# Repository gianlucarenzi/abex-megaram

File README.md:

Atari MegaRAM Cart for ABEX
=========================

This is a Atari MegaRAM Cart board, designed for the Atari PBI & ECI Bus EXtender
or ABEX for short.

This Atari MegaRAM is a PortB/PIA emulator which can expand the internal
memory of the Atari, using the memory mapped scheme used in the 80s/90s
like CompyShop, RAMbo and others.

Rendered Images
===============
# Front
# Back
# Overall

Hardware License
================
Copyright (C) 2018/2019 Gianluca Renzi <gianlucarenzi@eurek.it> <icjtqr@gmail.com>

The hardware of this project is released as free/open hardware under the
Creative Commons Attribution Share-Alike license. See `LICENSE.hw` for details.

Firmware License
================
Copyright (C) 2019 Gianluca Renzi <icjtqr@gmail.com>

The microcontroller firmware of this project is released as free software,
under the terms of the GNU General Public License v3, or later.  See
`LICENSE.sw` for details.

Software License
================
The host software (amigafloppy tool) is released as free software, under the
terms of the GNU General Public License v3, or later. See `LICENSE.sw` or licence.txt for
details.

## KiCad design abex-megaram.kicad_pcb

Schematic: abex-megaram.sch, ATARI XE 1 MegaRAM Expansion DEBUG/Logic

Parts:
C1: 100n; C_1206_HandSoldering
FT232RPi.1: CONN_01X03; Pin_Header_Straight_1x03
JP1: CONN_01X02; Pin_Header_Straight_1x02
JP2: CONN_01X04; Pin_Header_Angled_1x04
P1: 0877159106; BUS_PCIexpress_64pin
P2, P3, P4, P5: CONN_01X01; MountingHole
R1: 100K; R_1206_HandSoldering
R2: 0; R_1206_HandSoldering
SW1: SW_Push; SW_SPST_FSMSM_3D

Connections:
GND: C1.1, FT232RPi.1.1, JP1.2, JP2.1, P1.A1, P1.A5, P1.A9, P1.A13, P1.A17, P1.A21, P1.A25, P1.A29, P1.A32, P1.B17, P1.B21, P1.B25, R2.2, SW1.1; also elsewhere on the board
SWDCLK: JP2.3, P1.B29; also elsewhere on the board
SWDIO: JP2.2, P1.B27; also elsewhere on the board
SWDRST: C1.2, JP1.1, P1.B31, R1.1, SW1.2; also elsewhere on the board
UART_RX: FT232RPi.1.2; also elsewhere on the board
UART_TX: FT232RPi.1.3; also elsewhere on the board
VCC_3V3: JP2.4, P1.A3, P1.A7, P1.A11, P1.A15, P1.A19, P1.A23, P1.A27, P1.B19, P1.B23, R1.2; also elsewhere on the board
mA0: P1.B32; also elsewhere on the board
mA1: P1.B30; also elsewhere on the board
mA2: P1.B28; also elsewhere on the board
mA3: P1.B26; also elsewhere on the board
mA4: P1.B24; also elsewhere on the board
mA5: P1.B22; also elsewhere on the board
mA6: P1.B20; also elsewhere on the board
mA7: P1.B18; also elsewhere on the board
mA8: P1.B16; also elsewhere on the board
mA9: P1.B14; also elsewhere on the board
mA10: P1.B12; also elsewhere on the board
mA11: P1.B10; also elsewhere on the board
mA12: P1.B8; also elsewhere on the board
mA13: P1.B6; also elsewhere on the board
mA14: P1.B4; also elsewhere on the board
mA15: P1.B2; also elsewhere on the board
mAUDIO: P1.A6, R2.1
mD0: P1.B15; also elsewhere on the board
mD1: P1.B13; also elsewhere on the board
mD2: P1.B11; also elsewhere on the board
mD3: P1.B9; also elsewhere on the board
mD4: P1.B7; also elsewhere on the board
mD5: P1.B5; also elsewhere on the board
mD6: P1.B3; also elsewhere on the board
mD7: P1.B1; also elsewhere on the board
mPHI2: P1.A4; also elsewhere on the board
mR/~W: P1.A10; also elsewhere on the board
mRD4: P1.A24; also elsewhere on the board
mRD5: P1.A28; also elsewhere on the board
~mCCTL: P1.A30; also elsewhere on the board
~mD1XX: P1.A18; also elsewhere on the board
~mEXSEL: P1.A12; also elsewhere on the board
~mHALT: P1.A16; also elsewhere on the board
~mIRQ: P1.A14; also elsewhere on the board
~mMPD: P1.A20; also elsewhere on the board
~mREF: P1.A8; also elsewhere on the board
~mRST: P1.A2; also elsewhere on the board
~mS4: P1.A22; also elsewhere on the board
~mS5: P1.A26; also elsewhere on the board

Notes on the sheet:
DEBUG/PROGRAMMING SECTION MEMORY
MOUNTING HOLES
RESET BUTTON MEM
EXTENDED BUS PINS ARE CONNECTED IN THE SLOT BUT LEFT UNTRACKED
DNP
ABEX PCI EXPRESS CARD CONNECTOR 64 PIN
A31 is +5VDC. We do not need here

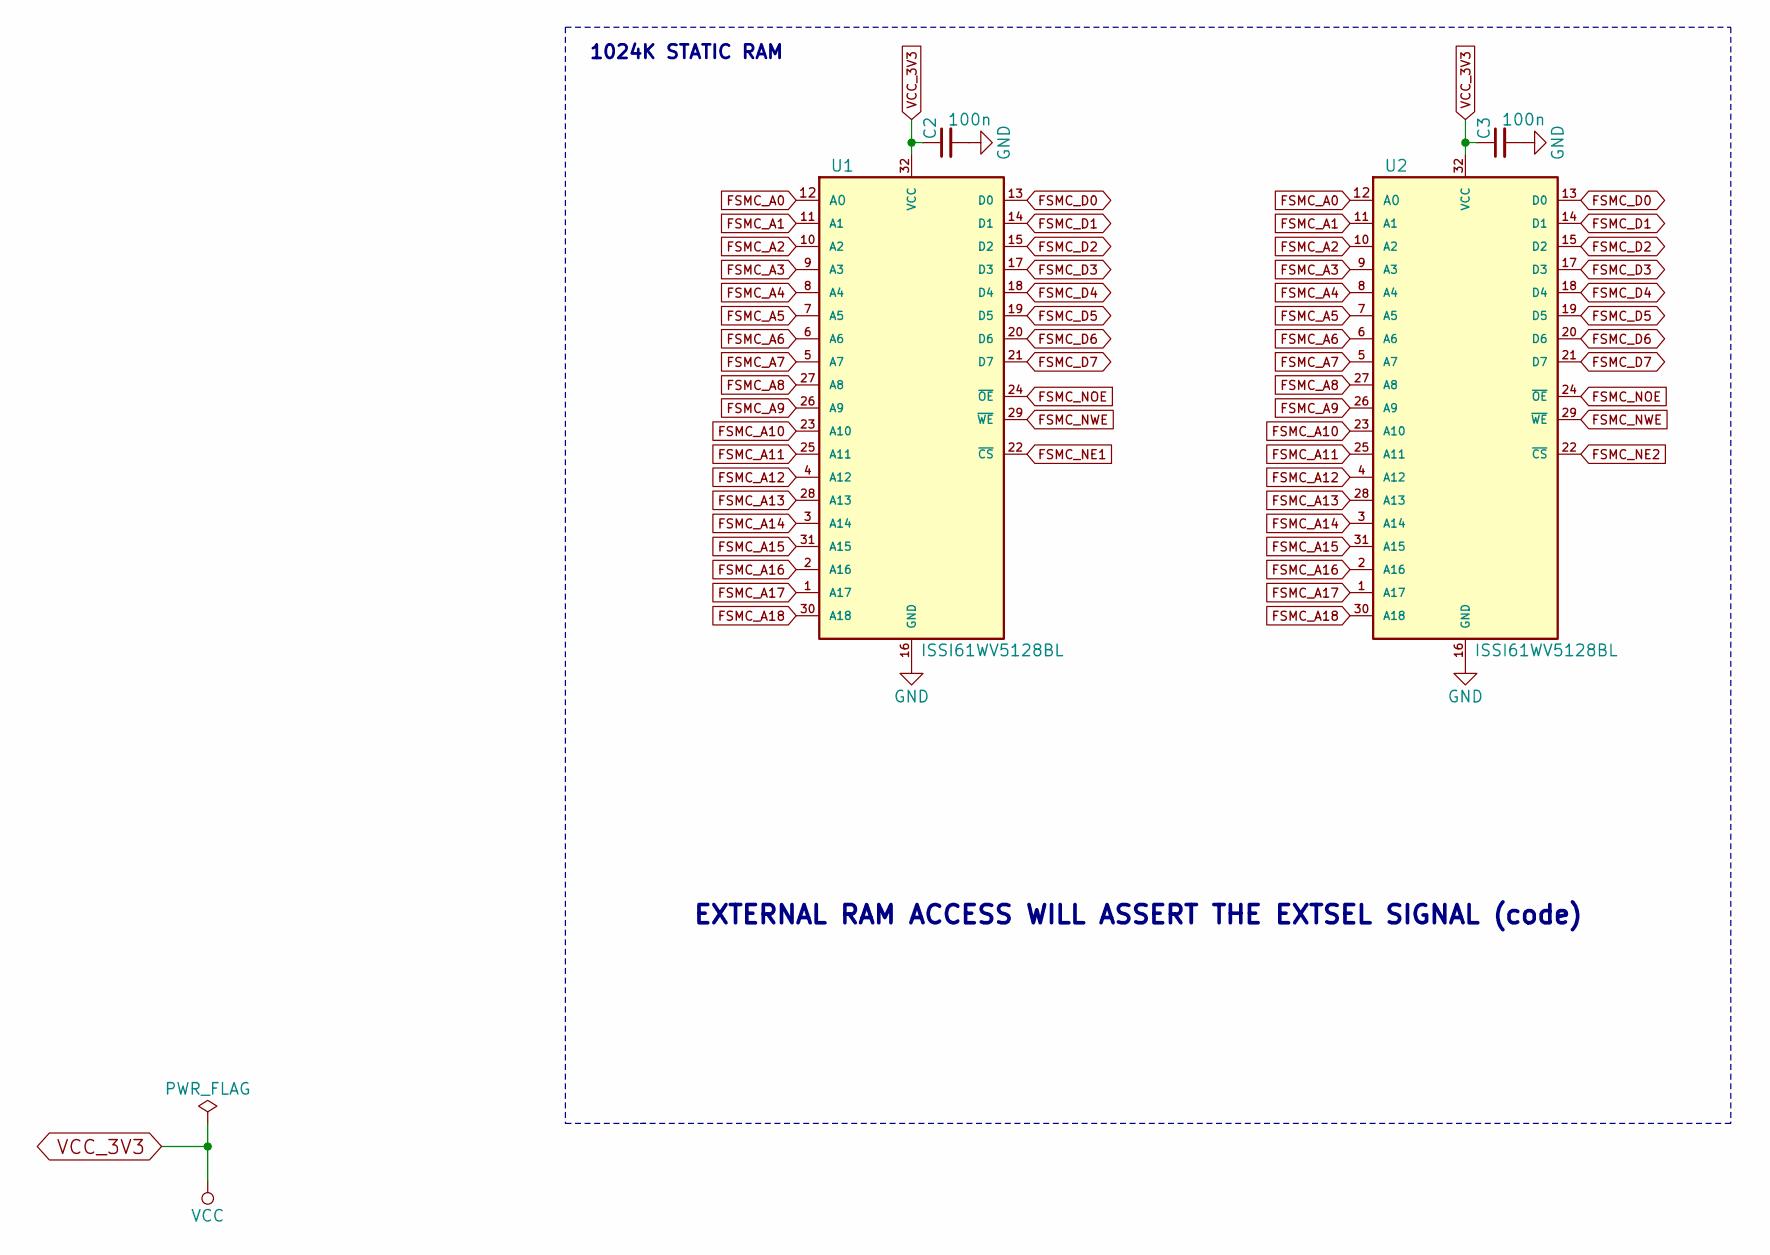
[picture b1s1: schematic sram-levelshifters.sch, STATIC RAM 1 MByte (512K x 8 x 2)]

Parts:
C2, C3: 100n; C_1206_HandSoldering
U1, U2: ISSI61WV5128BL; SOP-32L-20.5x11.30-1.27mm

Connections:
FSMC_A0: U1.12 (A0), U2.12 (A0); also elsewhere on the board
FSMC_A1: U1.11 (A1), U2.11 (A1); also elsewhere on the board
FSMC_A2: U1.10 (A2), U2.10 (A2); also elsewhere on the board
FSMC_A3: U1.9 (A3), U2.9 (A3); also elsewhere on the board
FSMC_A4: U1.8 (A4), U2.8 (A4); also elsewhere on the board
FSMC_A5: U1.7 (A5), U2.7 (A5); also elsewhere on the board
FSMC_A6: U1.6 (A6), U2.6 (A6); also elsewhere on the board
FSMC_A7: U1.5 (A7), U2.5 (A7); also elsewhere on the board
FSMC_A8: U1.27 (A8), U2.27 (A8); also elsewhere on the board
FSMC_A9: U1.26 (A9), U2.26 (A9); also elsewhere on the board
FSMC_A10: U1.23 (A10), U2.23 (A10); also elsewhere on the board
FSMC_A11: U1.25 (A11), U2.25 (A11); also elsewhere on the board
FSMC_A12: U1.4 (A12), U2.4 (A12); also elsewhere on the board
FSMC_A13: U1.28 (A13), U2.28 (A13); also elsewhere on the board
FSMC_A14: U1.3 (A14), U2.3 (A14); also elsewhere on the board
FSMC_A15: U1.31 (A15), U2.31 (A15); also elsewhere on the board
FSMC_A16: U1.2 (A16), U2.2 (A16); also elsewhere on the board
FSMC_A17: U1.1 (A17), U2.1 (A17); also elsewhere on the board
FSMC_A18: U1.30 (A18), U2.30 (A18); also elsewhere on the board
FSMC_D0: U1.13 (D0), U2.13 (D0); also elsewhere on the board
FSMC_D1: U1.14 (D1), U2.14 (D1); also elsewhere on the board
FSMC_D2: U1.15 (D2), U2.15 (D2); also elsewhere on the board
FSMC_D3: U1.17 (D3), U2.17 (D3); also elsewhere on the board
FSMC_D4: U1.18 (D4), U2.18 (D4); also elsewhere on the board
FSMC_D5: U1.19 (D5), U2.19 (D5); also elsewhere on the board
FSMC_D6: U1.20 (D6), U2.20 (D6); also elsewhere on the board
FSMC_D7: U1.21 (D7), U2.21 (D7); also elsewhere on the board
FSMC_NE1: U1.22 (~CS); also elsewhere on the board
FSMC_NE2: U2.22 (~CS); also elsewhere on the board
FSMC_NOE: U1.24 (~OE), U2.24 (~OE); also elsewhere on the board
FSMC_NWE: U1.29 (~WE), U2.29 (~WE); also elsewhere on the board
GND: C2.2, C3.2, U1.16 (GND), U2.16 (GND); also elsewhere on the board
VCC_3V3: C2.1, C3.1, U1.32 (VCC), U2.32 (VCC); also elsewhere on the board

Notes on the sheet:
1024K STATIC RAM
EXTERNAL RAM ACCESS WILL ASSERT THE EXTSEL SIGNAL (code)

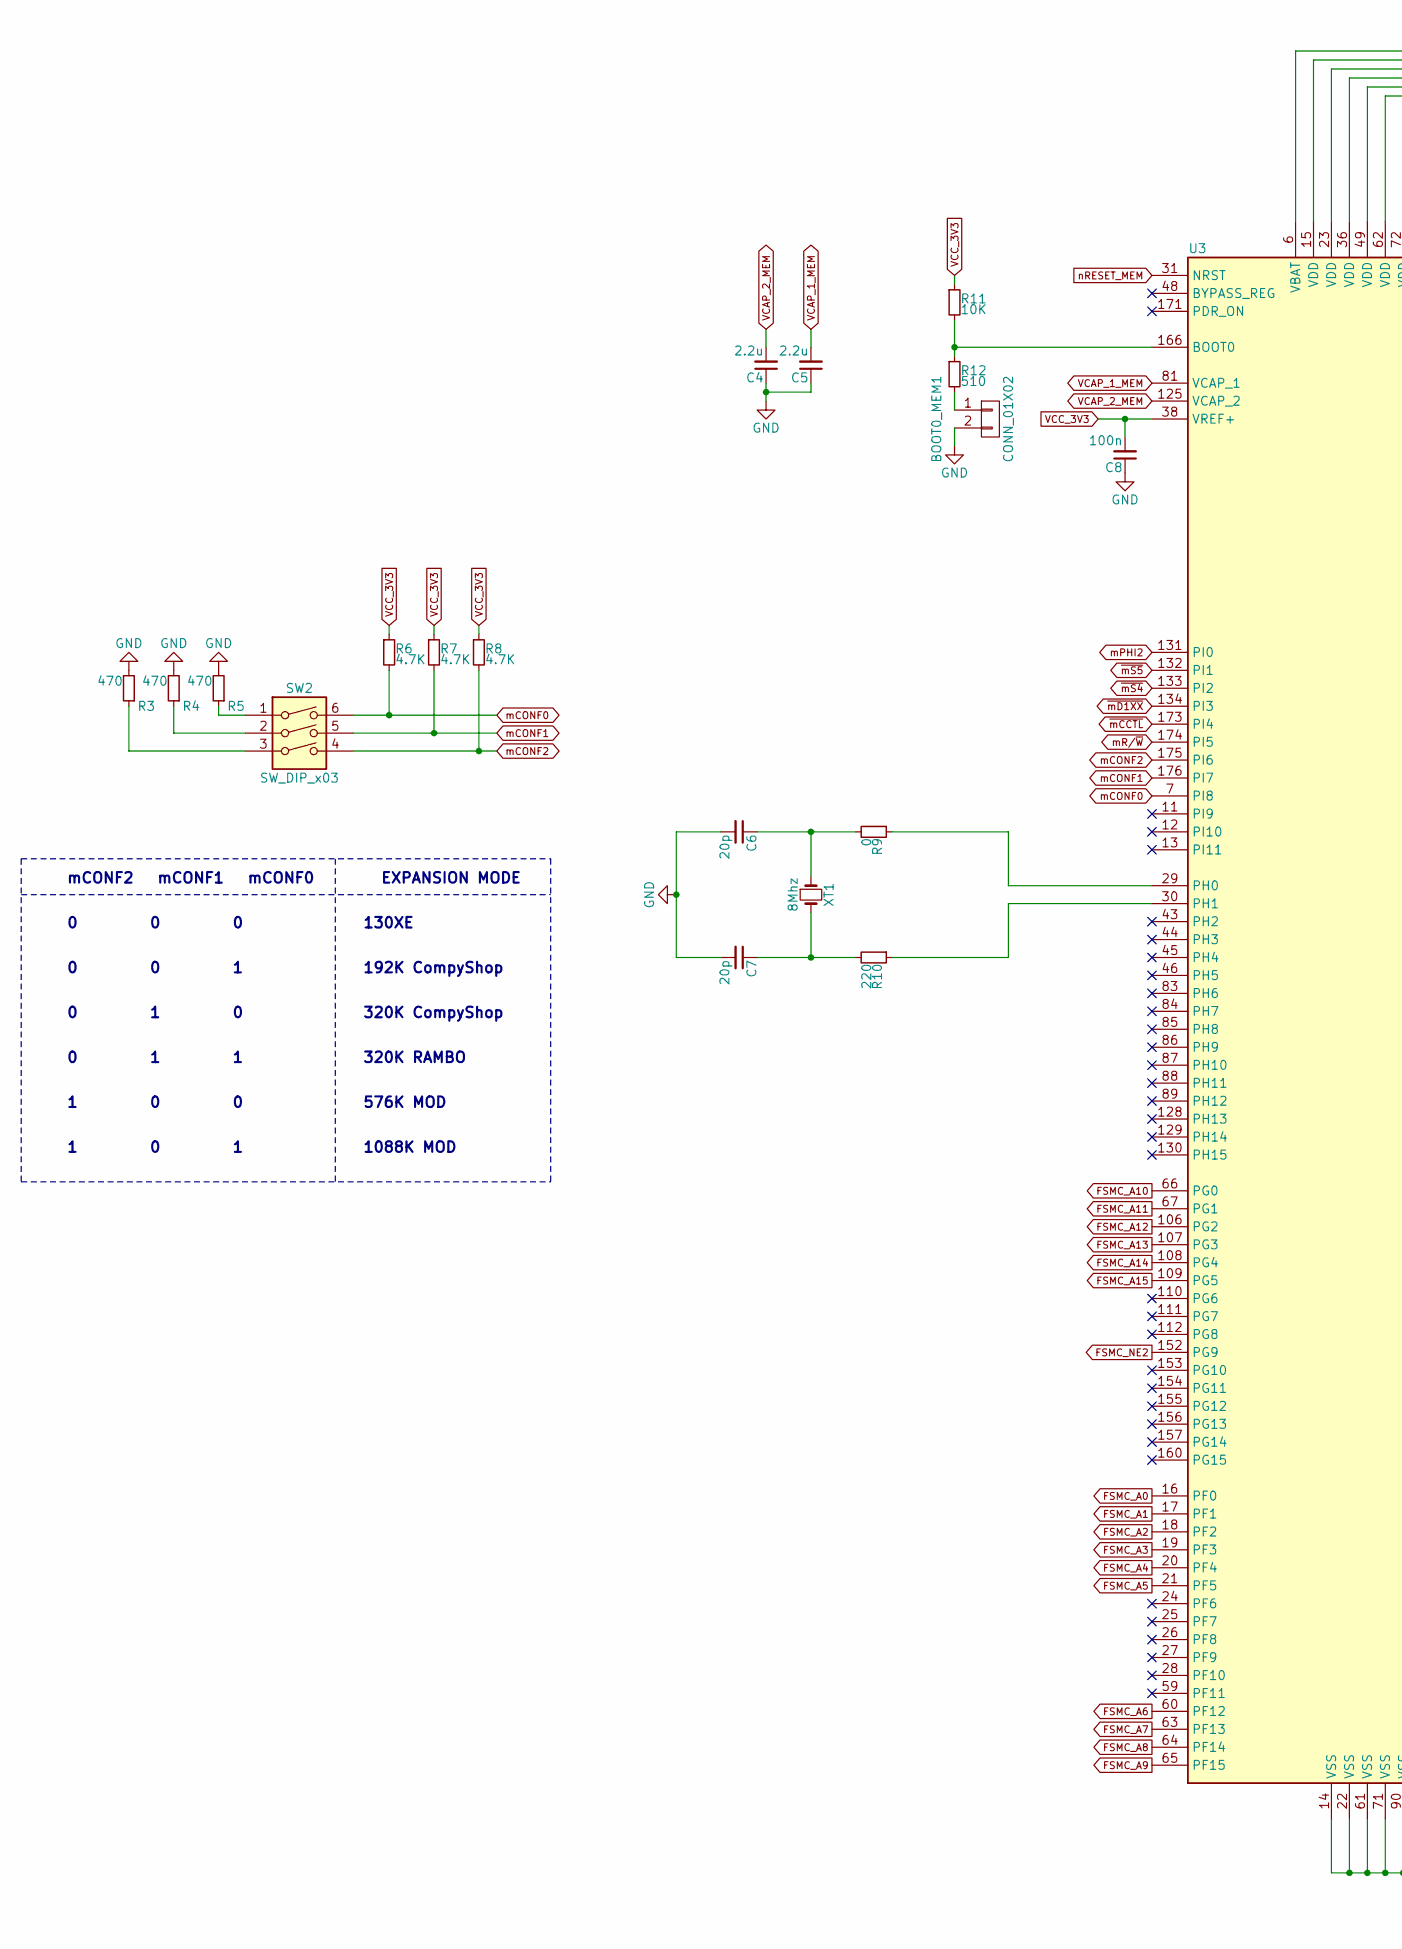
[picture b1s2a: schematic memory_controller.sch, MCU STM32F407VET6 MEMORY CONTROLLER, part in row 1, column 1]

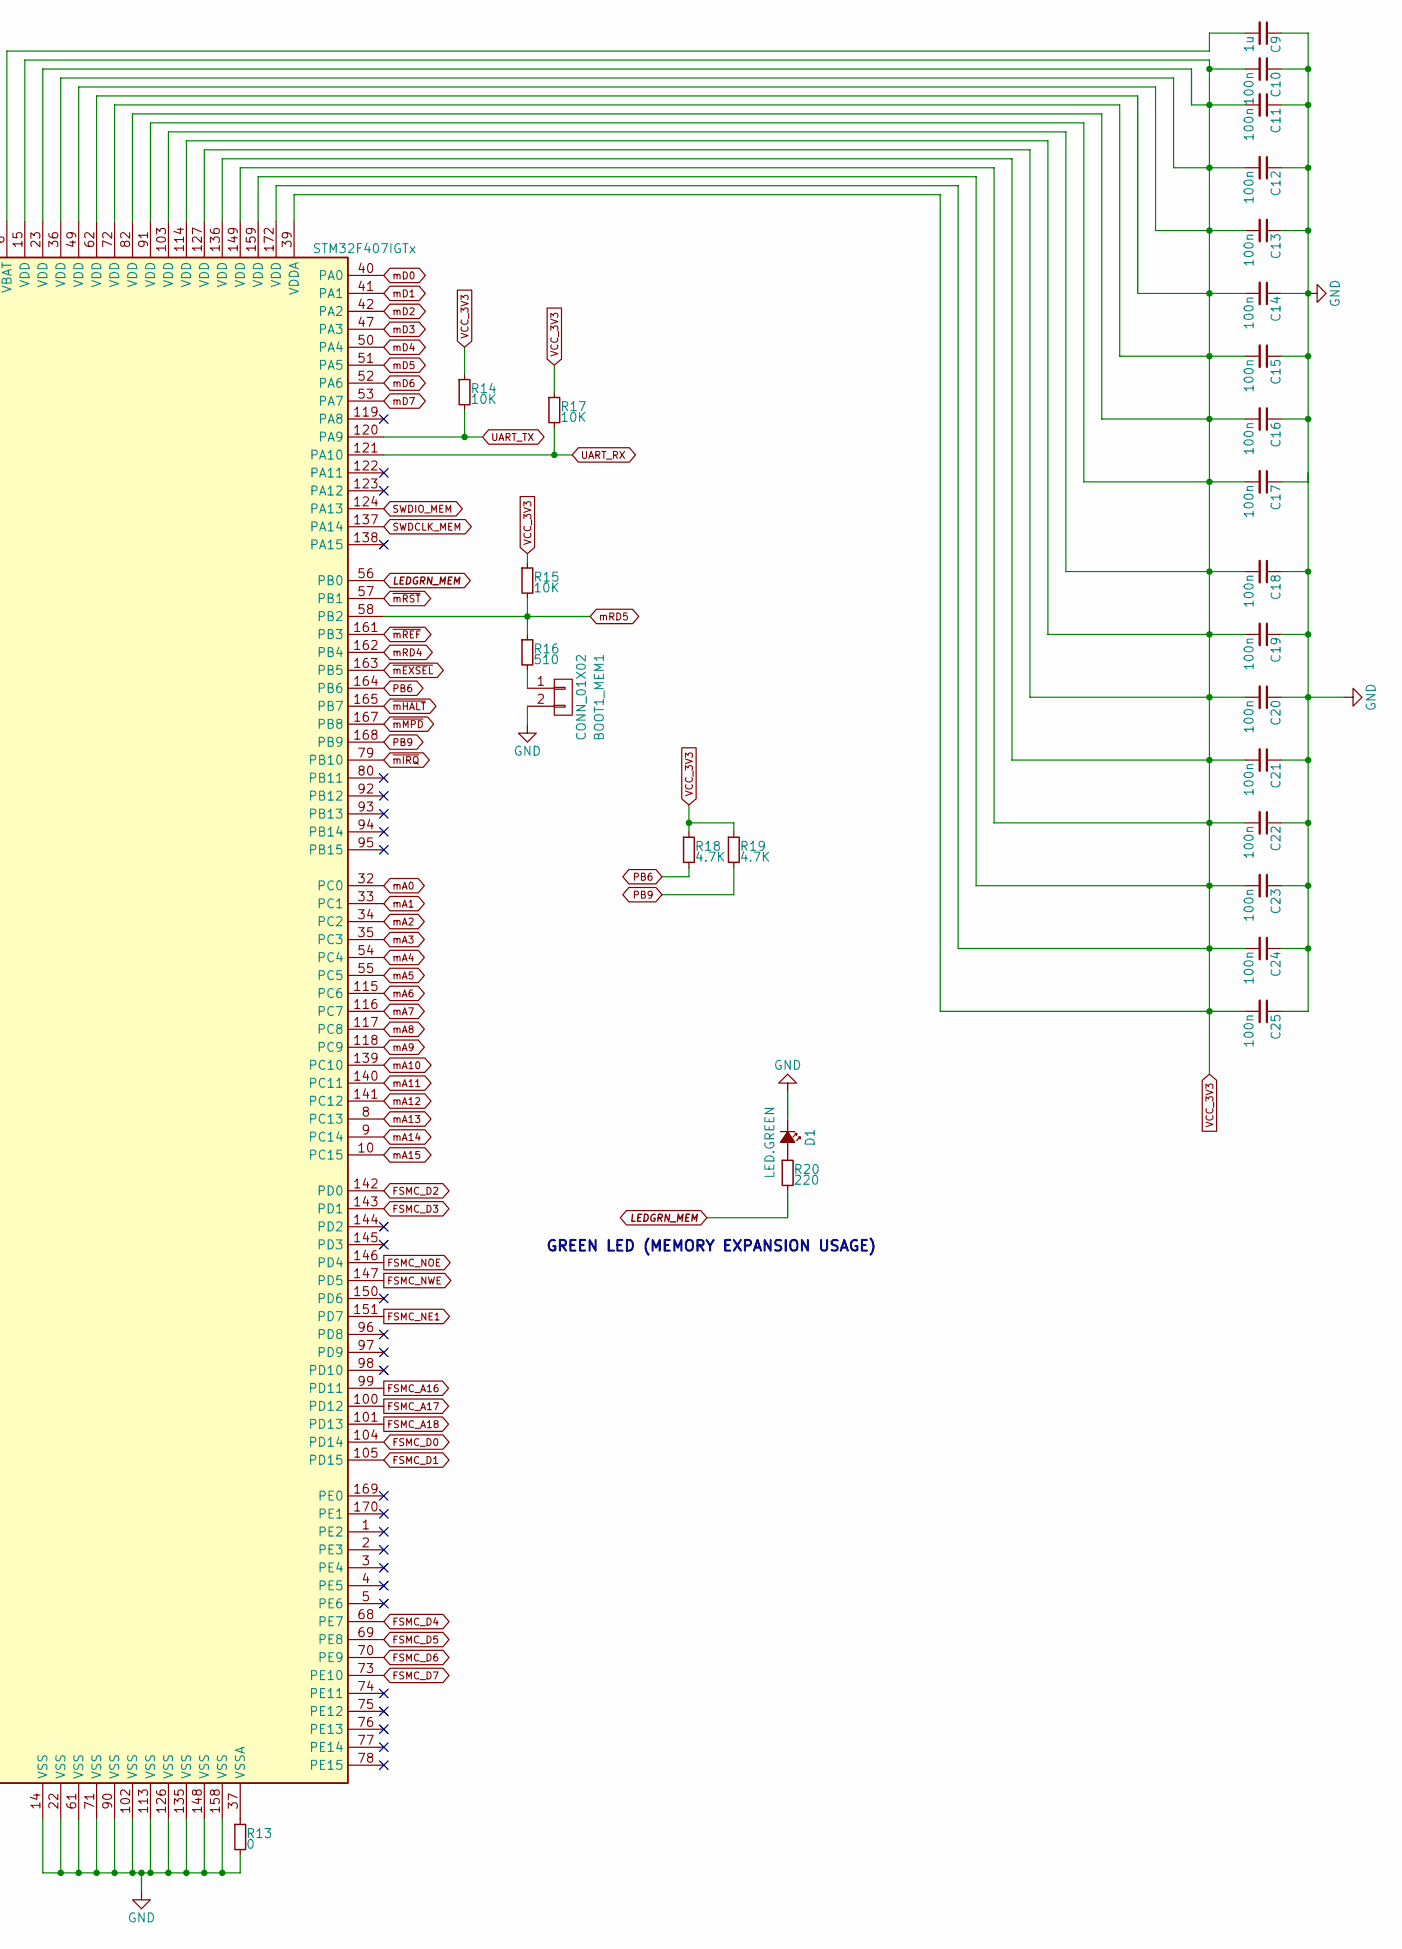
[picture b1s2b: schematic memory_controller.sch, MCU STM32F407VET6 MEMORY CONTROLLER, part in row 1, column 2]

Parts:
BOOT0_MEM1, BOOT1_MEM1: CONN_01X02; Pin_Header_Straight_1x02
C4, C5: 2.2u; C_1206_HandSoldering
C6, C7: 20p; C_1206_HandSoldering
C8, C10, C11, C12, C13, C14, C15, C16, C17, C18, C19, C20, C21, C22, C23, C24, C25: 100n; C_1206_HandSoldering
C9: 1u; C_1206_HandSoldering
D1: LED.GREEN; LED_1206
R3, R4, R5: 470; R_1206_HandSoldering
R6, R7, R8, R18, R19: 4.7K; R_1206_HandSoldering
R9, R13: 0; R_1206_HandSoldering
R10, R20: 220; R_1206_HandSoldering
R11, R14, R15, R17: 10K; R_1206_HandSoldering
R12, R16: 510; R_1206_HandSoldering
SW2: SW_DIP_x03; SW_DIP_SPSTx03_Slide_9.78x9.8mm_W8.61mm_P2.54mm
U3: STM32F407IGTx; LQFP-176_24x24mm_Pitch0.5mm
XT1: 8Mhz; Crystal_HC49-4H_Vertical_3D

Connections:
FSMC_A0: U3.16 (PF0); also elsewhere on the board
FSMC_A1: U3.17 (PF1); also elsewhere on the board
FSMC_A2: U3.18 (PF2); also elsewhere on the board
FSMC_A3: U3.19 (PF3); also elsewhere on the board
FSMC_A4: U3.20 (PF4); also elsewhere on the board
FSMC_A5: U3.21 (PF5); also elsewhere on the board
FSMC_A6: U3.60 (PF12); also elsewhere on the board
FSMC_A7: U3.63 (PF13); also elsewhere on the board
FSMC_A8: U3.64 (PF14); also elsewhere on the board
FSMC_A9: U3.65 (PF15); also elsewhere on the board
FSMC_A10: U3.66 (PG0); also elsewhere on the board
FSMC_A11: U3.67 (PG1); also elsewhere on the board
FSMC_A12: U3.106 (PG2); also elsewhere on the board
FSMC_A13: U3.107 (PG3); also elsewhere on the board
FSMC_A14: U3.108 (PG4); also elsewhere on the board
FSMC_A15: U3.109 (PG5); also elsewhere on the board
FSMC_A16: U3.99 (PD11); also elsewhere on the board
FSMC_A17: U3.100 (PD12); also elsewhere on the board
FSMC_A18: U3.101 (PD13); also elsewhere on the board
FSMC_D0: U3.104 (PD14); also elsewhere on the board
FSMC_D1: U3.105 (PD15); also elsewhere on the board
FSMC_D2: U3.142 (PD0); also elsewhere on the board
FSMC_D3: U3.143 (PD1); also elsewhere on the board
FSMC_D4: U3.68 (PE7); also elsewhere on the board
FSMC_D5: U3.69 (PE8); also elsewhere on the board
FSMC_D6: U3.70 (PE9); also elsewhere on the board
FSMC_D7: U3.73 (PE10); also elsewhere on the board
FSMC_NE1: U3.151 (PD7); also elsewhere on the board
FSMC_NE2: U3.152 (PG9); also elsewhere on the board
FSMC_NOE: U3.146 (PD4); also elsewhere on the board
FSMC_NWE: U3.147 (PD5); also elsewhere on the board
GND: BOOT0_MEM1.2, BOOT1_MEM1.2, C4.1, C5.1, C6.2, C7.2, C8.1, C9.1, C10.1, C11.1, C12.1, C13.1, C14.1, C15.1, C16.1, C17.1, C18.1, C19.1, C20.1, C21.1, C22.1, C23.1, C24.1, C25.1, D1.1 (K), R3.2, R4.2, R5.2, R13.2, U3.14 (VSS), U3.22 (VSS), U3.61 (VSS), U3.71 (VSS), U3.90 (VSS), U3.102 (VSS), U3.113 (VSS), U3.126 (VSS), U3.135 (VSS), U3.148 (VSS), U3.158 (VSS); also elsewhere on the board
LEDGRN_MEM: R20.2, U3.56 (PB0)
unnamed: BOOT0_MEM1.1, R12.2
unnamed: BOOT1_MEM1.1, R16.2
unnamed: C6.1, R9.2, XT1.1
unnamed: C7.1, R10.2, XT1.2
unnamed: C9.2, U3.6 (VBAT)
unnamed: D1.2 (A), R20.1
unnamed: R3.1, SW2.3
unnamed: R4.1, SW2.2
unnamed: R5.1, SW2.1
unnamed: R9.1, U3.29 (PH0)
unnamed: R10.1, U3.30 (PH1)
unnamed: R11.2, R12.1, U3.166 (BOOT0)
unnamed: R13.1, U3.37 (VSSA)
PB6: R18.2, U3.164 (PB6)
PB9: R19.2, U3.168 (PB9)
SWDCLK: U3.137 (PA14); also elsewhere on the board
SWDIO: U3.124 (PA13); also elsewhere on the board
SWDRST: U3.31 (NRST); also elsewhere on the board
UART_RX: R17.2, U3.121 (PA10); also elsewhere on the board
UART_TX: R14.2, U3.120 (PA9); also elsewhere on the board
VCAP_1_MEM: C5.2, U3.81 (VCAP_1)
VCAP_2_MEM: C4.2, U3.125 (VCAP_2)
VCC_3V3: C8.2, C10.2, C11.2, C12.2, C13.2, C14.2, C15.2, C16.2, C17.2, C18.2, C19.2, C20.2, C21.2, C22.2, C23.2, C24.2, C25.2, R6.1, R7.1, R8.1, R11.1, R14.1, R15.1, R17.1, R18.1, R19.1, U3.15 (VDD), U3.23 (VDD), U3.36 (VDD), U3.38 (VREF+), U3.39 (VDDA), U3.49 (VDD), U3.62 (VDD), U3.72 (VDD), U3.82 (VDD), U3.91 (VDD), U3.103 (VDD), U3.114 (VDD), U3.127 (VDD), U3.136 (VDD), U3.149 (VDD), U3.159 (VDD), U3.172 (VDD); also elsewhere on the board
mA0: U3.32 (PC0); also elsewhere on the board
mA1: U3.33 (PC1); also elsewhere on the board
mA2: U3.34 (PC2); also elsewhere on the board
mA3: U3.35 (PC3); also elsewhere on the board
mA4: U3.54 (PC4); also elsewhere on the board
mA5: U3.55 (PC5); also elsewhere on the board
mA6: U3.115 (PC6); also elsewhere on the board
mA7: U3.116 (PC7); also elsewhere on the board
mA8: U3.117 (PC8); also elsewhere on the board
mA9: U3.118 (PC9); also elsewhere on the board
mA10: U3.139 (PC10); also elsewhere on the board
mA11: U3.140 (PC11); also elsewhere on the board
mA12: U3.141 (PC12); also elsewhere on the board
mA13: U3.8 (PC13); also elsewhere on the board
mA14: U3.9 (PC14); also elsewhere on the board
mA15: U3.10 (PC15); also elsewhere on the board
mCONF0: R6.2, SW2.6, U3.7 (PI8)
mCONF1: R7.2, SW2.5, U3.176 (PI7)
mCONF2: R8.2, SW2.4, U3.175 (PI6)
mD0: U3.40 (PA0); also elsewhere on the board
mD1: U3.41 (PA1); also elsewhere on the board
mD2: U3.42 (PA2); also elsewhere on the board
mD3: U3.47 (PA3); also elsewhere on the board
mD4: U3.50 (PA4); also elsewhere on the board
mD5: U3.51 (PA5); also elsewhere on the board
mD6: U3.52 (PA6); also elsewhere on the board
mD7: U3.53 (PA7); also elsewhere on the board
mPHI2: U3.131 (PI0); also elsewhere on the board
mR/~W: U3.174 (PI5); also elsewhere on the board
mRD4: U3.162 (PB4); also elsewhere on the board
mRD5: R15.2, R16.1, U3.58 (PB2); also elsewhere on the board
~mCCTL: U3.173 (PI4); also elsewhere on the board
~mD1XX: U3.134 (PI3); also elsewhere on the board
~mEXSEL: U3.163 (PB5); also elsewhere on the board
~mHALT: U3.165 (PB7); also elsewhere on the board
~mIRQ: U3.79 (PB10); also elsewhere on the board
~mMPD: U3.167 (PB8); also elsewhere on the board
~mREF: U3.161 (PB3); also elsewhere on the board
~mRST: U3.57 (PB1); also elsewhere on the board
~mS4: U3.133 (PI2); also elsewhere on the board
~mS5: U3.132 (PI1); also elsewhere on the board

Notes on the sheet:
GREEN LED (MEMORY EXPANSION USAGE)
mCONF2 mCONF1 mCONF0
0 0 0
0 0 1
0 1 0
0 1 1
1 0 1
130XE
192K CompyShop
320K CompyShop
320K RAMBO
1088K MOD
EXPANSION MODE
1 0 0
576K MOD

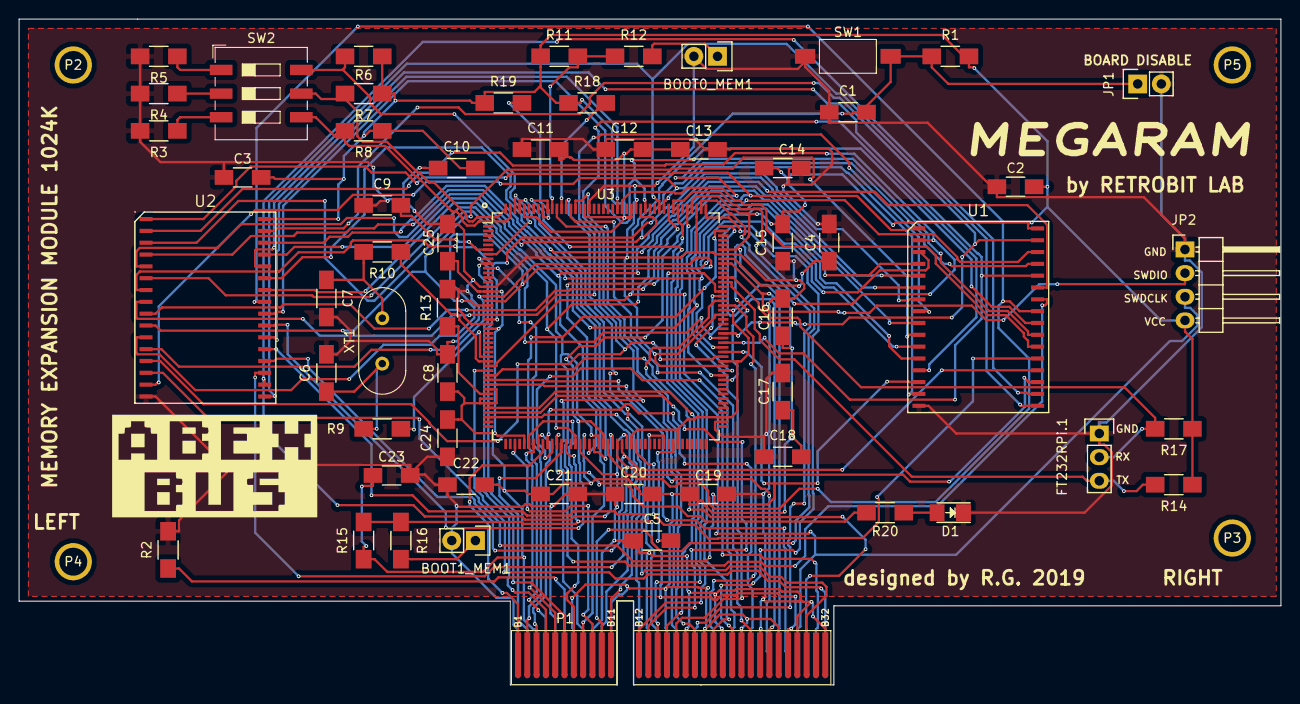
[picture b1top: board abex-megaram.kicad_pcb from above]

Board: 2 copper layers, 135.5 x 71.5 mm, 62 parts (0 on the bottom side), 98 nets.

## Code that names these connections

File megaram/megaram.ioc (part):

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Mcu.Name=STM32F429I(E-G)Tx
Mcu.Package=LQFP176
Mcu.UserName=STM32F429IGTx
PA0/WKUP.GPIOParameters=GPIO_Label
PA0/WKUP.GPIO_Label=m_D0
PA0/WKUP.Signal=GPIO_Input
PA1.GPIOParameters=GPIO_Label
PA1.GPIO_Label=m_D1
PA1.Signal=GPIO_Input
PA10.GPIOParameters=GPIO_Label
PA10.GPIO_Label=DEBUG_RX
PA10.Mode=Asynchronous
PA10.Signal=USART1_RX
PA2.GPIOParameters=GPIO_Label
PA2.GPIO_Label=m_D2
PA2.Signal=GPIO_Input
PA3.GPIOParameters=GPIO_Label
PA3.GPIO_Label=m_D3
PA3.Signal=GPIO_Input
PA4.GPIOParameters=GPIO_Label
PA4.GPIO_Label=m_D4
PA4.Signal=GPIO_Input
PA5.GPIOParameters=GPIO_Label
PA5.GPIO_Label=m_D5
PA5.Signal=GPIO_Input
PA6.GPIOParameters=GPIO_Label
PA6.GPIO_Label=m_D6
PA6.Signal=GPIO_Input
PA7.GPIOParameters=GPIO_Label
PA7.GPIO_Label=m_D7
PA7.Signal=GPIO_Input
PA9.GPIOParameters=GPIO_Label
PA9.GPIO_Label=DEBUG_TX
PA9.Mode=Asynchronous
PA9.Signal=USART1_TX
PB0.GPIOParameters=GPIO_Speed,GPIO_Label
PB0.GPIO_Label=LED
PB0.GPIO_Speed=GPIO_SPEED_FREQ_VERY_HIGH
PB0.Signal=GPIO_Output
PB1.GPIOParameters=GPIO_Speed,PinState,GPIO_Label
PB1.GPIO_Label=m_RST
PB1.GPIO_Speed=GPIO_SPEED_FREQ_VERY_HIGH
PB1.PinState=GPIO_PIN_SET
PB1.Signal=GPIO_Output
PB10.GPIOParameters=GPIO_Speed,PinState,GPIO_Label
PB10.GPIO_Label=m_IRQ
PB10.GPIO_Speed=GPIO_SPEED_FREQ_VERY_HIGH
PB10.PinState=GPIO_PIN_SET
PB10.Signal=GPIO_Output
PB2/BOOT1.GPIOParameters=GPIO_Speed,PinState,GPIO_Label
PB2/BOOT1.GPIO_Label=m_RD5
PB2/BOOT1.GPIO_Speed=GPIO_SPEED_FREQ_VERY_HIGH
PB2/BOOT1.PinState=GPIO_PIN_SET
PB2/BOOT1.Signal=GPIO_Output
PB3.GPIOParameters=GPIO_Speed,PinState,GPIO_Label
PB3.GPIO_Label=m_REF
PB3.GPIO_Speed=GPIO_SPEED_FREQ_VERY_HIGH
PB3.PinState=GPIO_PIN_SET
PB3.Signal=GPIO_Output
PB4.GPIOParameters=GPIO_Speed,PinState,GPIO_Label
PB4.GPIO_Label=m_RD4
PB4.GPIO_Speed=GPIO_SPEED_FREQ_VERY_HIGH
PB4.PinState=GPIO_PIN_SET
PB4.Signal=GPIO_Output
PB5.GPIOParameters=GPIO_Speed,PinState,GPIO_Label
PB5.GPIO_Label=m_EXSEL
PB5.GPIO_Speed=GPIO_SPEED_FREQ_VERY_HIGH
PB5.PinState=GPIO_PIN_SET
PB5.Signal=GPIO_Output
PB6.GPIOParameters=GPIO_Speed,GPIO_Label
PB6.GPIO_Label=PB6
PB6.GPIO_Speed=GPIO_SPEED_FREQ_VERY_HIGH
PB6.Signal=GPIO_Output
PB7.GPIOParameters=GPIO_Speed,PinState,GPIO_Label
PB7.GPIO_Label=m_HALT
PB7.GPIO_Speed=GPIO_SPEED_FREQ_VERY_HIGH
PB7.PinState=GPIO_PIN_SET
PB7.Signal=GPIO_Output
PB8.GPIOParameters=GPIO_Speed,PinState,GPIO_Label
PB8.GPIO_Label=m_MPD
PB8.GPIO_Speed=GPIO_SPEED_FREQ_VERY_HIGH
PB8.PinState=GPIO_PIN_SET
PB8.Signal=GPIO_Output
PB9.GPIOParameters=GPIO_Speed,GPIO_Label
PB9.GPIO_Label=PB9
PB9.GPIO_Speed=GPIO_SPEED_FREQ_VERY_HIGH
PB9.Signal=GPIO_Output
PC0.GPIOParameters=GPIO_Label
PC0.GPIO_Label=m_A0
PC0.Signal=GPIO_Input
PC1.GPIOParameters=GPIO_Label
PC1.GPIO_Label=m_A1
PC1.Signal=GPIO_Input
PC10.GPIOParameters=GPIO_Label
PC10.GPIO_Label=m_A10
PC10.Signal=GPIO_Input
PC11.GPIOParameters=GPIO_Label
PC11.GPIO_Label=m_A11
PC11.Signal=GPIO_Input
PC12.GPIOParameters=GPIO_Label
PC12.GPIO_Label=m_A12
PC12.Signal=GPIO_Input
PC13.GPIOParameters=GPIO_Label
PC13.GPIO_Label=m_A13
PC13.Signal=GPIO_Input
PC14/OSC32_IN.GPIOParameters=GPIO_Label
PC14/OSC32_IN.GPIO_Label=m_A14
PC14/OSC32_IN.Signal=GPIO_Input
PC15/OSC32_OUT.GPIOParameters=GPIO_Label
PC15/OSC32_OUT.GPIO_Label=m_A15
PC15/OSC32_OUT.Signal=GPIO_Input
PC2.GPIOParameters=GPIO_Label
PC2.GPIO_Label=m_A2
PC2.Signal=GPIO_Input
PC3.GPIOParameters=GPIO_Label
PC3.GPIO_Label=m_A3
PC3.Signal=GPIO_Input
PC4.GPIOParameters=GPIO_Label
PC4.GPIO_Label=m_A4
PC4.Signal=GPIO_Input
PC5.GPIOParameters=GPIO_Label
PC5.GPIO_Label=m_A5
PC5.Signal=GPIO_Input
PC6.GPIOParameters=GPIO_Label
PC6.GPIO_Label=m_A6
PC6.Signal=GPIO_Input
PC7.GPIOParameters=GPIO_Label
PC7.GPIO_Label=m_A7
PC7.Signal=GPIO_Input
PC8.GPIOParameters=GPIO_Label
PC8.GPIO_Label=m_A8
PC8.Signal=GPIO_Input
PC9.GPIOParameters=GPIO_Label
PC9.GPIO_Label=m_A9
PC9.Signal=GPIO_Input
PD0.Signal=FMC_D2_DA2
PD1.Signal=FMC_D3_DA3
PD11.Signal=FMC_A16_CLE
PD12.Signal=FMC_A17_ALE
PD13.Signal=FMC_A18
PD14.Signal=FMC_D0_DA0
PD15.Signal=FMC_D1_DA1
PD4.Signal=FMC_NOE
PD5.Signal=FMC_NWE
PD7.Mode=NorPsramChipSelect1_1
PD7.Signal=FMC_NE1
PE10.Signal=FMC_D7_DA7
PE3.Signal=FMC_A19
PE7.Signal=FMC_D4_DA4
PE8.Signal=FMC_D5_DA5
PE9.Signal=FMC_D6_DA6
PF0.Signal=FMC_A0
PF1.Signal=FMC_A1
PF12.Signal=FMC_A6
PF13.Signal=FMC_A7
PF14.Signal=FMC_A8
PF15.Signal=FMC_A9
PF2.Signal=FMC_A2
PF3.Signal=FMC_A3
PF4.Signal=FMC_A4
PF5.Signal=FMC_A5
PG0.Signal=FMC_A10
PG1.Signal=FMC_A11
PG2.Signal=FMC_A12
PG3.Signal=FMC_A13
PG4.Signal=FMC_A14_BA0
PG5.Signal=FMC_A15_BA1
PH0/OSC_IN.Mode=HSE-External-Clock-Source
PH0/OSC_IN.Signal=RCC_OSC_IN
PH1/OSC_OUT.Mode=HSE-External-Clock-Source
PH1/OSC_OUT.Signal=RCC_OSC_OUT
PI0.GPIOParameters=GPIO_Label
PI0.GPIO_Label=m_PHI2
PI0.Signal=GPIO_Input
PI1.GPIOParameters=GPIO_Label
PI1.GPIO_Label=m_S5
PI1.Signal=GPIO_Input
PI2.GPIOParameters=GPIO_Label
PI2.GPIO_Label=m_S4
PI2.Signal=GPIO_Input
PI3.GPIOParameters=GPIO_Label
PI3.GPIO_Label=m_D1XX
PI3.Signal=GPIO_Input
PI4.GPIOParameters=GPIO_Label
PI4.GPIO_Label=m_CCTL
PI4.Signal=GPIO_Input
PI5.GPIOParameters=GPIO_Label
PI5.GPIO_Label=m_RW
PI5.Signal=GPIO_Input
PI6.GPIOParameters=GPIO_Label
PI6.GPIO_Label=CONF0
PI6.Signal=GPIO_Input
PI7.GPIOParameters=GPIO_Label
PI7.GPIO_Label=CONF1
PI7.Signal=GPIO_Input
PI8.GPIOParameters=GPIO_Label
PI8.GPIO_Label=CONF2
PI8.Signal=GPIO_Input
RCC.HSE_VALUE=8000000
RCC.SYSCLKFreq_VALUE=180000000
RCC.SYSCLKSource=RCC_SYSCLKSOURCE_PLLCLK
board=custom

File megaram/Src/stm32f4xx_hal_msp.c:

/* USER CODE BEGIN Header */
/**
  ******************************************************************************
  * File Name          : stm32f4xx_hal_msp.c
  * Description        : This file provides code for the MSP Initialization 
  *                      and de-Initialization codes.
  ******************************************************************************
  * @attention
  *
  * <h2><center>&copy; Copyright (c) 2019 STMicroelectronics.
  * All rights reserved.</center></h2>
  *
  * This software component is licensed by ST under BSD 3-Clause license,
  * the "License"; You may not use this file except in compliance with the
  * License. You may obtain a copy of the License at:
  *                        opensource.org/licenses/BSD-3-Clause
  *
  ******************************************************************************
  */
/* USER CODE END Header */

/* Includes ------------------------------------------------------------------*/
#include "main.h"
/* USER CODE BEGIN Includes */

/* USER CODE END Includes */

/* Private typedef -----------------------------------------------------------*/
/* USER CODE BEGIN TD */

/* USER CODE END TD */

/* Private define ------------------------------------------------------------*/
/* USER CODE BEGIN Define */
 
/* USER CODE END Define */

/* Private macro -------------------------------------------------------------*/
/* USER CODE BEGIN Macro */

/* USER CODE END Macro */

/* Private variables ---------------------------------------------------------*/
/* USER CODE BEGIN PV */

/* USER CODE END PV */

/* Private function prototypes -----------------------------------------------*/
/* USER CODE BEGIN PFP */

/* USER CODE END PFP */

/* External functions --------------------------------------------------------*/
/* USER CODE BEGIN ExternalFunctions */

/* USER CODE END ExternalFunctions */

/* USER CODE BEGIN 0 */

/* USER CODE END 0 */
/**
  * Initializes the Global MSP.
  */
void HAL_MspInit(void)
{
  /* USER CODE BEGIN MspInit 0 */

  /* USER CODE END MspInit 0 */

  __HAL_RCC_SYSCFG_CLK_ENABLE();
  __HAL_RCC_PWR_CLK_ENABLE();

  /* System interrupt init*/

  /* USER CODE BEGIN MspInit 1 */

  /* USER CODE END MspInit 1 */
}

/**
* @brief UART MSP Initialization
* This function configures the hardware resources used in this example
* @param huart: UART handle pointer
* @retval None
*/
void HAL_UART_MspInit(UART_HandleTypeDef* huart)
{
  GPIO_InitTypeDef GPIO_InitStruct = {0};
  if(huart->Instance==USART1)
  {
  /* USER CODE BEGIN USART1_MspInit 0 */

  /* USER CODE END USART1_MspInit 0 */
    /* Peripheral clock enable */
    __HAL_RCC_USART1_CLK_ENABLE();
  
    __HAL_RCC_GPIOA_CLK_ENABLE();
    /**USART1 GPIO Configuration    
    PA9     ------> USART1_TX
    PA10     ------> USART1_RX 
    */
    GPIO_InitStruct.Pin = GPIO_PIN_9|GPIO_PIN_10;
    GPIO_InitStruct.Mode = GPIO_MODE_AF_PP;
    GPIO_InitStruct.Pull = GPIO_PULLUP;
    GPIO_InitStruct.Speed = GPIO_SPEED_FREQ_VERY_HIGH;
    GPIO_InitStruct.Alternate = GPIO_AF7_USART1;
    HAL_GPIO_Init(GPIOA, &GPIO_InitStruct);

  /* USER CODE BEGIN USART1_MspInit 1 */

  /* USER CODE END USART1_MspInit 1 */
  }

}

/**
* @brief UART MSP De-Initialization
* This function freeze the hardware resources used in this example
* @param huart: UART handle pointer
* @retval None
*/
void HAL_UART_MspDeInit(UART_HandleTypeDef* huart)
{
  if(huart->Instance==USART1)
  {
  /* USER CODE BEGIN USART1_MspDeInit 0 */

  /* USER CODE END USART1_MspDeInit 0 */
    /* Peripheral clock disable */
    __HAL_RCC_USART1_CLK_DISABLE();
  
    /**USART1 GPIO Configuration    
    PA9     ------> USART1_TX
    PA10     ------> USART1_RX 
    */
    HAL_GPIO_DeInit(GPIOA, GPIO_PIN_9|GPIO_PIN_10);

  /* USER CODE BEGIN USART1_MspDeInit 1 */

  /* USER CODE END USART1_MspDeInit 1 */
  }

}

static uint32_t FSMC_Initialized = 0;

static void HAL_FSMC_MspInit(void){
  /* USER CODE BEGIN FSMC_MspInit 0 */

  /* USER CODE END FSMC_MspInit 0 */
  GPIO_InitTypeDef GPIO_InitStruct ={0};
  if (FSMC_Initialized) {
    return;
  }
  FSMC_Initialized = 1;
  /* Peripheral clock enable */
  __HAL_RCC_FSMC_CLK_ENABLE();
  
  /** FSMC GPIO Configuration  
  PF0   ------> FSMC_A0
  PF1   ------> FSMC_A1
  PF2   ------> FSMC_A2
  PF3   ------> FSMC_A3
  PF4   ------> FSMC_A4
  PF5   ------> FSMC_A5
  PF12   ------> FSMC_A6
  PF13   ------> FSMC_A7
  PF14   ------> FSMC_A8
  PF15   ------> FSMC_A9
  PG0   ------> FSMC_A10
  PG1   ------> FSMC_A11
  PE7   ------> FSMC_D4
  PE8   ------> FSMC_D5
  PE9   ------> FSMC_D6
  PE10   ------> FSMC_D7
  PD11   ------> FSMC_A16
  PD12   ------> FSMC_A17
  PD13   ------> FSMC_A18
  PD14   ------> FSMC_D0
  PD15   ------> FSMC_D1
  PG2   ------> FSMC_A12
  PG3   ------> FSMC_A13
  PG4   ------> FSMC_A14
  PG5   ------> FSMC_A15
  PD0   ------> FSMC_D2
  PD1   ------> FSMC_D3
  PD4   ------> FSMC_NOE
  PD5   ------> FSMC_NWE
  PD7   ------> FSMC_NE1
  PG9   ------> FSMC_NE2
  */
  GPIO_InitStruct.Pin = GPIO_PIN_0|GPIO_PIN_1|GPIO_PIN_2|GPIO_PIN_3 
                          |GPIO_PIN_4|GPIO_PIN_5|GPIO_PIN_12|GPIO_PIN_13 
                          |GPIO_PIN_14|GPIO_PIN_15;
  GPIO_InitStruct.Mode = GPIO_MODE_AF_PP;
  GPIO_InitStruct.Pull = GPIO_NOPULL;
  GPIO_InitStruct.Speed = GPIO_SPEED_FREQ_VERY_HIGH;
  GPIO_InitStruct.Alternate = GPIO_AF12_FSMC;
  HAL_GPIO_Init(GPIOF, &GPIO_InitStruct);

  GPIO_InitStruct.Pin = GPIO_PIN_0|GPIO_PIN_1|GPIO_PIN_2|GPIO_PIN_3 
                          |GPIO_PIN_4|GPIO_PIN_5|GPIO_PIN_9;
  GPIO_InitStruct.Mode = GPIO_MODE_AF_PP;
  GPIO_InitStruct.Pull = GPIO_NOPULL;
  GPIO_InitStruct.Speed = GPIO_SPEED_FREQ_VERY_HIGH;
  GPIO_InitStruct.Alternate = GPIO_AF12_FSMC;
  HAL_GPIO_Init(GPIOG, &GPIO_InitStruct);

  GPIO_InitStruct.Pin = GPIO_PIN_7|GPIO_PIN_8|GPIO_PIN_9|GPIO_PIN_10;
  GPIO_InitStruct.Mode = GPIO_MODE_AF_PP;
  GPIO_InitStruct.Pull = GPIO_NOPULL;
  GPIO_InitStruct.Speed = GPIO_SPEED_FREQ_VERY_HIGH;
  GPIO_InitStruct.Alternate = GPIO_AF12_FSMC;
  HAL_GPIO_Init(GPIOE, &GPIO_InitStruct);

  GPIO_InitStruct.Pin = GPIO_PIN_11|GPIO_PIN_12|GPIO_PIN_13|GPIO_PIN_14 
                          |GPIO_PIN_15|GPIO_PIN_0|GPIO_PIN_1|GPIO_PIN_4 
                          |GPIO_PIN_5|GPIO_PIN_7;
  GPIO_InitStruct.Mode = GPIO_MODE_AF_PP;
  GPIO_InitStruct.Pull = GPIO_NOPULL;
  GPIO_InitStruct.Speed = GPIO_SPEED_FREQ_VERY_HIGH;
  GPIO_InitStruct.Alternate = GPIO_AF12_FSMC;
  HAL_GPIO_Init(GPIOD, &GPIO_InitStruct);

  /* USER CODE BEGIN FSMC_MspInit 1 */

  /* USER CODE END FSMC_MspInit 1 */
}

void HAL_SRAM_MspInit(SRAM_HandleTypeDef* hsram){
  /* USER CODE BEGIN SRAM_MspInit 0 */

  /* USER CODE END SRAM_MspInit 0 */
  HAL_FSMC_MspInit();
  /* USER CODE BEGIN SRAM_MspInit 1 */

  /* USER CODE END SRAM_MspInit 1 */
}

static uint32_t FSMC_DeInitialized = 0;

static void HAL_FSMC_MspDeInit(void){
  /* USER CODE BEGIN FSMC_MspDeInit 0 */

  /* USER CODE END FSMC_MspDeInit 0 */
  if (FSMC_DeInitialized) {
    return;
  }
  FSMC_DeInitialized = 1;
  /* Peripheral clock enable */
  __HAL_RCC_FSMC_CLK_DISABLE();
  
  /** FSMC GPIO Configuration  
  PF0   ------> FSMC_A0
  PF1   ------> FSMC_A1
  PF2   ------> FSMC_A2
  PF3   ------> FSMC_A3
  PF4   ------> FSMC_A4
  PF5   ------> FSMC_A5
  PF12   ------> FSMC_A6
  PF13   ------> FSMC_A7
  PF14   ------> FSMC_A8
  PF15   ------> FSMC_A9
  PG0   ------> FSMC_A10
  PG1   ------> FSMC_A11
  PE7   ------> FSMC_D4
  PE8   ------> FSMC_D5
  PE9   ------> FSMC_D6
  PE10   ------> FSMC_D7
  PD11   ------> FSMC_A16
  PD12   ------> FSMC_A17
  PD13   ------> FSMC_A18
  PD14   ------> FSMC_D0
  PD15   ------> FSMC_D1
  PG2   ------> FSMC_A12
  PG3   ------> FSMC_A13
  PG4   ------> FSMC_A14
  PG5   ------> FSMC_A15
  PD0   ------> FSMC_D2
  PD1   ------> FSMC_D3
  PD4   ------> FSMC_NOE
  PD5   ------> FSMC_NWE
  PD7   ------> FSMC_NE1
  PG9   ------> FSMC_NE2
  */
  HAL_GPIO_DeInit(GPIOF, GPIO_PIN_0|GPIO_PIN_1|GPIO_PIN_2|GPIO_PIN_3 
                          |GPIO_PIN_4|GPIO_PIN_5|GPIO_PIN_12|GPIO_PIN_13 
                          |GPIO_PIN_14|GPIO_PIN_15);

  HAL_GPIO_DeInit(GPIOG, GPIO_PIN_0|GPIO_PIN_1|GPIO_PIN_2|GPIO_PIN_3 
                          |GPIO_PIN_4|GPIO_PIN_5|GPIO_PIN_9);

  HAL_GPIO_DeInit(GPIOE, GPIO_PIN_7|GPIO_PIN_8|GPIO_PIN_9|GPIO_PIN_10);

  HAL_GPIO_DeInit(GPIOD, GPIO_PIN_11|GPIO_PIN_12|GPIO_PIN_13|GPIO_PIN_14 
                          |GPIO_PIN_15|GPIO_PIN_0|GPIO_PIN_1|GPIO_PIN_4 
                          |GPIO_PIN_5|GPIO_PIN_7);

  /* USER CODE BEGIN FSMC_MspDeInit 1 */

  /* USER CODE END FSMC_MspDeInit 1 */
}

void HAL_SRAM_MspDeInit(SRAM_HandleTypeDef* hsram){
  /* USER CODE BEGIN SRAM_MspDeInit 0 */

  /* USER CODE END SRAM_MspDeInit 0 */
  HAL_FSMC_MspDeInit();
  /* USER CODE BEGIN SRAM_MspDeInit 1 */

  /* USER CODE END SRAM_MspDeInit 1 */
}

/* USER CODE BEGIN 1 */

/* USER CODE END 1 */

/************************ (C) COPYRIGHT STMicroelectronics *****END OF FILE****/

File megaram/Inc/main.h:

/* USER CODE BEGIN Header */
/**
  ******************************************************************************
  * @file           : main.h
  * @brief          : Header for main.c file.
  *                   This file contains the common defines of the application.
  ******************************************************************************
  * @attention
  *
  * <h2><center>&copy; Copyright (c) 2019 STMicroelectronics.
  * All rights reserved.</center></h2>
  *
  * This software component is licensed by ST under BSD 3-Clause license,
  * the "License"; You may not use this file except in compliance with the
  * License. You may obtain a copy of the License at:
  *                        opensource.org/licenses/BSD-3-Clause
  *
  ******************************************************************************
  */
/* USER CODE END Header */

/* Define to prevent recursive inclusion -------------------------------------*/
#ifndef __MAIN_H
#define __MAIN_H

#ifdef __cplusplus
extern "C" {
#endif

/* Includes ------------------------------------------------------------------*/
#include "stm32f4xx_hal.h"

/* Private includes ----------------------------------------------------------*/
/* USER CODE BEGIN Includes */

/* USER CODE END Includes */

/* Exported types ------------------------------------------------------------*/
/* USER CODE BEGIN ET */

/* USER CODE END ET */

/* Exported constants --------------------------------------------------------*/
/* USER CODE BEGIN EC */

/* USER CODE END EC */

/* Exported macro ------------------------------------------------------------*/
/* USER CODE BEGIN EM */

/* USER CODE END EM */

/* Exported functions prototypes ---------------------------------------------*/
void Error_Handler(void);

/* USER CODE BEGIN EFP */

/* USER CODE END EFP */

/* Private defines -----------------------------------------------------------*/
#define mPHI2_Pin GPIO_PIN_8
#define mPHI2_GPIO_Port GPIOI
#define mA13_Pin GPIO_PIN_13
#define mA13_GPIO_Port GPIOC
#define mA14_Pin GPIO_PIN_14
#define mA14_GPIO_Port GPIOC
#define mA15_Pin GPIO_PIN_15
#define mA15_GPIO_Port GPIOC
#define mA0_Pin GPIO_PIN_0
#define mA0_GPIO_Port GPIOC
#define mA1_Pin GPIO_PIN_1
#define mA1_GPIO_Port GPIOC
#define mA2_Pin GPIO_PIN_2
#define mA2_GPIO_Port GPIOC
#define mA3_Pin GPIO_PIN_3
#define mA3_GPIO_Port GPIOC
#define mD0_Pin GPIO_PIN_0
#define mD0_GPIO_Port GPIOA
#define mD1_Pin GPIO_PIN_1
#define mD1_GPIO_Port GPIOA
#define mD2_Pin GPIO_PIN_2
#define mD2_GPIO_Port GPIOA
#define mD3_Pin GPIO_PIN_3
#define mD3_GPIO_Port GPIOA
#define mD4_Pin GPIO_PIN_4
#define mD4_GPIO_Port GPIOA
#define mD5_Pin GPIO_PIN_5
#define mD5_GPIO_Port GPIOA
#define mD6_Pin GPIO_PIN_6
#define mD6_GPIO_Port GPIOA
#define mD7_Pin GPIO_PIN_7
#define mD7_GPIO_Port GPIOA
#define mA4_Pin GPIO_PIN_4
#define mA4_GPIO_Port GPIOC
#define mA5_Pin GPIO_PIN_5
#define mA5_GPIO_Port GPIOC
#define LED_Pin GPIO_PIN_0
#define LED_GPIO_Port GPIOB
#define mRST_Pin GPIO_PIN_1
#define mRST_GPIO_Port GPIOB
#define mRD5_Pin GPIO_PIN_2
#define mRD5_GPIO_Port GPIOB
#define mIRQ_Pin GPIO_PIN_10
#define mIRQ_GPIO_Port GPIOB
#define mA6_Pin GPIO_PIN_6
#define mA6_GPIO_Port GPIOC
#define mA7_Pin GPIO_PIN_7
#define mA7_GPIO_Port GPIOC
#define mA8_Pin GPIO_PIN_8
#define mA8_GPIO_Port GPIOC
#define mA9_Pin GPIO_PIN_9
#define mA9_GPIO_Port GPIOC
#define mPHI2I0_Pin GPIO_PIN_0
#define mPHI2I0_GPIO_Port GPIOI
#define mS5_Pin GPIO_PIN_1
#define mS5_GPIO_Port GPIOI
#define mS4_Pin GPIO_PIN_2
#define mS4_GPIO_Port GPIOI
#define mD1XX_Pin GPIO_PIN_3
#define mD1XX_GPIO_Port GPIOI
#define mA10_Pin GPIO_PIN_10
#define mA10_GPIO_Port GPIOC
#define mA11_Pin GPIO_PIN_11
#define mA11_GPIO_Port GPIOC
#define mA12_Pin GPIO_PIN_12
#define mA12_GPIO_Port GPIOC
#define mREF_Pin GPIO_PIN_3
#define mREF_GPIO_Port GPIOB
#define mRD4_Pin GPIO_PIN_4
#define mRD4_GPIO_Port GPIOB
#define mEXSEL_Pin GPIO_PIN_5
#define mEXSEL_GPIO_Port GPIOB
#define PB6_Pin GPIO_PIN_6
#define PB6_GPIO_Port GPIOB
#define mHALT_Pin GPIO_PIN_7
#define mHALT_GPIO_Port GPIOB
#define mMPD_Pin GPIO_PIN_8
#define mMPD_GPIO_Port GPIOB
#define PB9_Pin GPIO_PIN_9
#define PB9_GPIO_Port GPIOB
#define mCCTL_Pin GPIO_PIN_4
#define mCCTL_GPIO_Port GPIOI
#define mRW_Pin GPIO_PIN_5
#define mRW_GPIO_Port GPIOI
#define mCONF2_Pin GPIO_PIN_6
#define mCONF2_GPIO_Port GPIOI
#define mCONF1_Pin GPIO_PIN_7
#define mCONF1_GPIO_Port GPIOI
/* USER CODE BEGIN Private defines */

/* USER CODE END Private defines */

#ifdef __cplusplus
}
#endif

#endif /* __MAIN_H */

/************************ (C) COPYRIGHT STMicroelectronics *****END OF FILE****/
